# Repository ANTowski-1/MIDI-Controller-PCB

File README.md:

# MIDI-Controller-PCB

Before building using 1st revision think it through, but if you are interested in 2nd revision, it will probably be done in the end of the year, based on interest, so create an issue or write to me directly to let me know that you'd like to see it!

This Repo contains Ki-Cad projects of MIDI-Controller PCB.
Whole documentation can be found in separate repo: ANTowski-1/MIDI-Controller.
(As of end of September 2026, documentations is not made as for code still being developed)

This is an Hobbyist-made project, that isn't connected with MIDI Association in any way, apart from utilizing the MIDI 2.0 standard.

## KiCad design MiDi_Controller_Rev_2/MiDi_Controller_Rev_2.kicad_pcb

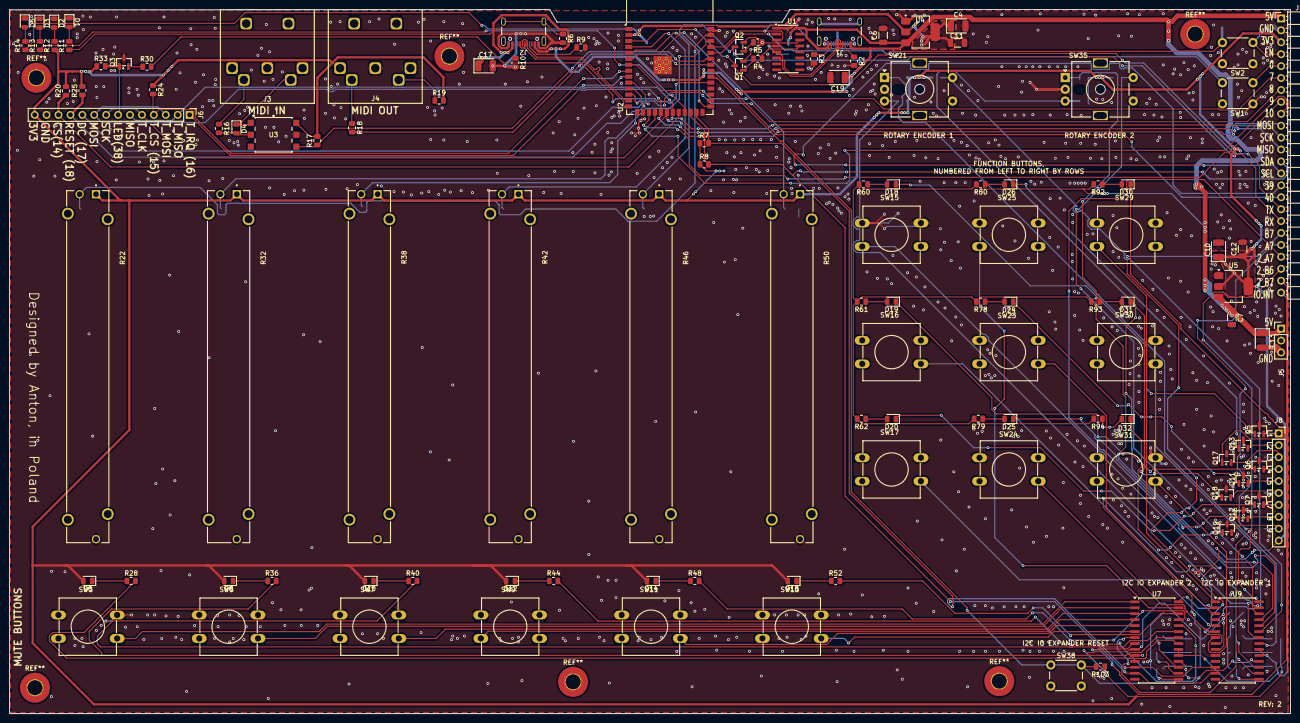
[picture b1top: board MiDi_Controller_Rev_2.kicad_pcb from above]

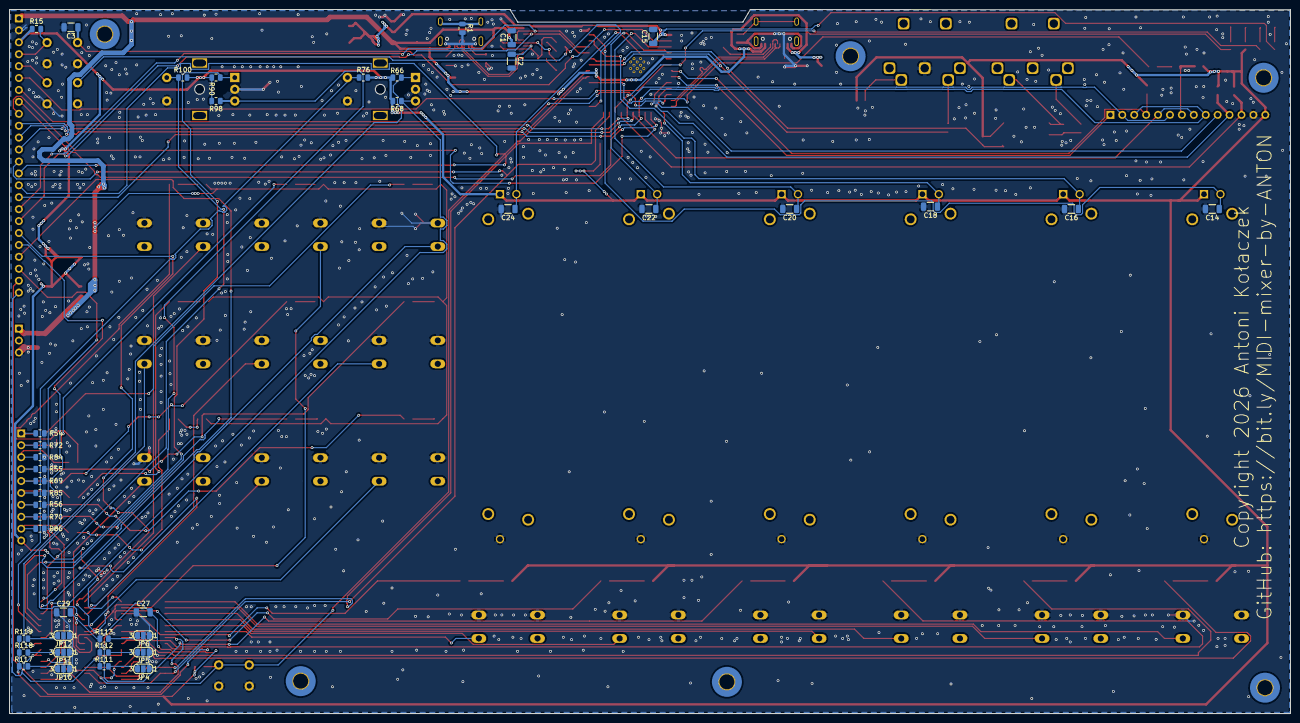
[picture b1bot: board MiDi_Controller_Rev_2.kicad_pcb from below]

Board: 2 copper layers, 272.9 x 150.0 mm, 161 parts (41 on the bottom side), 138 nets.

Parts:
C1, C2, C14, C15, C16, C18, C20, C22, C24: 100nF; C_1206_3216Metric
C3: 1u; C_1206_3216Metric
C4, C10: C_Polarized; CP_EIA-3528-21_Kemet-B
C6, C7, C11, C12, C27, C29: 100n; C_1206_3216Metric
C13, C17, C19: 10µ C_Polarized; CP_EIA-3528-21_Kemet-B
D1, D18, D19, D20, D24, D25, D26, D30, D31, D32: BLUE; LED_0805_2012Metric
D2, D5: GREEN; LED_0805_2012Metric
D3, D6, D8, D10, D12, D14, D16: RED; LED_0805_2012Metric
D4: D; D_0805_2012Metric
J1, J2: USB_C_Receptacle_USB2.0_16P; USB_C_Receptacle_GCT_USB4105-xx-A_16P_TopMnt_Horizontal
J3, J4: DIN-5; DIN-5-lumberg-0105
J5: Conn_01x03_Pin; PinHeader_1x03_P2.54mm_Vertical
J6: Display; PinHeader_1x14_P2.54mm_Vertical
J8: KEYPAD_LEDS; PinSocket_1x10_P2.54mm_Vertical
J10: Conn_01x24_Pin; PinHeader_1x24_P2.54mm_Horizontal
JP4, JP5, JP6, JP10, JP11, JP12: Jumper_3_Bridged12; SolderJumper-3_P1.3mm_Open_RoundedPad1.0x1.5mm_NumberLabels
Q1, Q2: BC817; SOT-23
Q3, Q5, Q6, Q7, Q11, Q12, Q13, Q17, Q18, Q19: NMOS; SOT-23
R1, R6: 1M; R_0805_2012Metric
R2, R3, R9, R10: 5k1; R_0805_2012Metric
R4, R5, R20, R24, R25, R30, R33, R54, R55, R56, R69, R70, R72, R84, R85, R86: 10K; R_0805_2012Metric
R7, R8: 4k7; R_0805_2012Metric
R11, R60, R61, R62, R78, R79, R80, R92, R93, R94: 110R; R_0805_2012Metric
R12, R14: 47R; R_0805_2012Metric
R13, R28, R36, R40, R44, R48, R52: 82R; R_0805_2012Metric
R15: 5.1K; R_0805_2012Metric
R16, R18: 220R; R_0805_2012Metric
R17: 680R; R_0805_2012Metric
R19: 33R; R_0805_2012Metric
R22, R32, R38, R42, R46, R50: PTA6043-2015DPB103; TRIM_PTA6043-2015DPB103
R66, R68, R76, R90, R98, R100, R103, R111, R112, R113, R117, R118, R119: 10k; R_0805_2012Metric
SW1, SW2: TS-1088-AR02016; SW_PUSH_6mm_H5mm
SW3, SW5, SW7, SW9, SW11, SW13, SW15, SW16, SW17, SW23, SW24, SW25, SW29, SW30, SW31: SW_Push; SW_PUSH-12mm
SW21, SW35: RotaryEncoder_Switch; RotaryEncoder_Alps_EC11E-Switch_Vertical_H20mm_MountingHoles
SW38: SW_Push; SW_PUSH_6mm_H4.3mm
U1: CH340C; SOIC-16_3.9x9.9mm_P1.27mm
U2: ESP32-S3-WROOM-1
U3: H11L1; H11L1STA_EVE
U4, U5: AMS1117-3.3; SOT-223-3_TabPin2
U7, U9: MCP23017x-x-SO; SOIC-28W_7.5x17.9mm_P1.27mm

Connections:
2_GPA0: R28.2, U7.21 (GPA0)
2_GPA1: R36.2, U7.22 (GPA1)
2_GPA2: R40.2, U7.23 (GPA2)
2_GPA3: R44.2, U7.24 (GPA3)
2_GPA4: R48.2, U7.25 (GPA4)
2_GPA5: R52.2, U7.26 (GPA5)
2_GPA6: SW25.2, U7.27 (GPA6)
2_GPA7: J10.21, U7.28 (GPA7)
2_GPB0: SW3.2, U7.1 (GPB0)
2_GPB1: SW5.2, U7.2 (GPB1)
2_GPB2: SW7.2, U7.3 (GPB2)
2_GPB3: SW9.2, U7.4 (GPB3)
2_GPB4: SW11.2, U7.5 (GPB4)
2_GPB5: SW13.2, U7.6 (GPB5)
2_GPB6: J10.22, U7.7 (GPB6)
2_GPB7: J10.23, U7.8 (GPB7)
+3V3: C10.1, C12.1, C27.2, C29.2, D6.2 (A), D8.2 (A), D10.2 (A), D12.2 (A), D14.2 (A), D16.2 (A), J6.14, J8.10, J10.3, R7.1, R8.1, R12.1, R15.1, R17.2, R19.2, R20.2, R22.1, R24.1, R25.2, R32.1, R33.1, R38.1, R42.1, R46.1, R50.1, R66.2, R68.2, R76.2, R90.2, R98.2, R100.2, R103.1, R111.1, R112.1, R113.1, R117.1, R118.1, R119.1, U3.6, U5.2 (VO), U7.9 (V_{DD}), U9.9 (V_{DD})
+5V: C1.1, C6.1, C7.1, C13.1, C17.1, C19.1, J1.A4 (VBUS), J1.A9 (VBUS), J1.B4 (VBUS), J1.B9 (VBUS), J2.A4 (VBUS), J2.A9 (VBUS), J2.B4 (VBUS), J2.B9 (VBUS), J5.1, J10.1, R11.1, R60.2, R61.2, R62.2, R78.2, R79.2, R80.2, R92.2, R93.2, R94.2, U1.16 (VCC), U4.3 (VI), U5.3 (VI)
A0: JP10.2 (C), U9.15 (A0)
A0_2: JP4.2 (C), U7.15 (A0)
A1: JP11.2 (C), U9.16 (A1)
A1_2: JP5.2 (C), U7.16 (A1)
A2: JP12.2 (C), U9.17 (A2)
A2_2: JP6.2 (C), U7.17 (A2)
D+: J2.A6 (D+), J2.B6 (D+), U2.14 (USB_D+)
D-: J2.A7 (D-), J2.B7 (D-), U2.13 (USB_D-)
DS+: J1.A6 (D+), J1.B6 (D+), U1.5 (UD+)
DS-: J1.A7 (D-), J1.B7 (D-), U1.6 (UD-)
EN: C3.1, J10.4, Q1.3 (C), R15.2, SW2.2, U2.3 (EN)
GND: C1.2, C2.2, C3.2, C4.2, C6.2, C7.2, C10.2, C11.2, C12.2, C13.2, C14.2, C15.2, C16.2, C17.2, C18.2, C19.2, C20.2, C22.2, C24.2, C27.1, C29.1, D1.1 (K), D2.1 (K), D3.1 (K), D5.1 (K), J1.A1 (GND), J1.A12 (GND), J1.B1 (GND), J1.B12 (GND), J2.A1 (GND), J2.A12 (GND), J2.B1 (GND), J2.B12 (GND), J4.2, J5.3, J6.13, J10.2, JP4.1 (A), JP5.1 (A), JP6.1 (A), JP10.1 (A), JP11.1 (A), JP12.1 (A), Q3.3 (S), Q5.3 (S), Q6.3 (S), Q7.3 (S), Q11.3 (S), Q12.3 (S), Q13.3 (S), Q17.3 (S), Q18.3 (S), Q19.3 (S), R1.2, R2.2, R3.2, R6.2, R9.2, R10.2, R22.3, R32.3, R38.3, R42.3, R46.3, R50.3, R54.1, R55.1, R56.1, R69.1, R70.1, R72.1, R84.1, R85.1, R86.1, SW1.1, SW2.1, SW3.1, SW5.1, SW7.1, SW9.1, SW11.1, SW13.1, SW15.1, SW16.1, SW17.1, SW21.C, SW21.S1, SW23.1, SW24.1, SW25.1, SW29.1, SW30.1, SW31.1, SW35.C, SW35.S1, SW38.2, U1.1 (GND), U2.1 (GND), U2.40 (GND), U2.41 (GND), U3.5, U4.1 (GND), U5.1 (GND), U7.10 (V_{SS}), U9.10 (V_{SS})
GPA0: R66.1, SW21.A, U9.21 (GPA0)
GPA1: R68.1, SW21.B, U9.22 (GPA1)
GPA2: R76.1, SW21.S2, U9.23 (GPA2)
GPA3: R90.1, SW35.A, U9.24 (GPA3)
GPA4: R98.1, SW35.B, U9.25 (GPA4)
GPA5: R100.1, SW35.S2, U9.26 (GPA5)
GPA6: SW15.2, U9.27 (GPA6)
GPA7: J10.20, U9.28 (GPA7)
GPB0: SW29.2, U9.1 (GPB0)
GPB1: SW16.2, U9.2 (GPB1)
GPB2: SW23.2, U9.3 (GPB2)
GPB3: SW30.2, U9.4 (GPB3)
GPB4: SW17.2, U9.5 (GPB4)
GPB5: SW24.2, U9.6 (GPB5)
GPB6: SW31.2, U9.7 (GPB6)
GPB7: J10.19, U9.8 (GPB7)
GPIO0: J10.5, Q2.3 (C), SW1.2, U2.27 (IO0)
GPIO1: C14.1, R22.2, U2.39 (IO1)
GPIO2: C16.1, R32.2, U2.38 (IO2)
GPIO3: C18.1, R38.2, U2.15 (IO3)
GPIO4: C20.1, R42.2, U2.4 (IO4)
GPIO5: C22.1, R46.2, U2.5 (IO5)
GPIO6: C24.1, R50.2, U2.6 (IO6)
GPIO7: J10.6, U2.7 (IO7)
GPIO8: J10.7, U2.12 (IO8)
GPIO9: J10.8, U2.17 (IO9)
GPIO10: J10.9, U2.18 (IO10)
GPIO11: J6.3, J6.9, J10.10, U2.19 (IO11)
GPIO12: J6.5, J6.8, J10.11, U2.20 (IO12)
GPIO13: J6.2, J6.6, J10.12, U2.21 (IO13)
GPIO14: J6.12, R20.1, U2.22 (IO14)
GPIO15: J6.4, R24.2, U2.8 (IO15)
GPIO16: J6.1, U2.9 (IO16)
GPIO17: J6.10, U2.10 (IO17)
GPIO18: J6.11, R25.1, U2.11 (IO18)
GPIO21: R13.1, U2.23 (IO21)
GPIO38: R30.2, U2.31 (IO38)
GPIO39: J10.15, R103.2, SW38.1, U2.32 (IO39), U7.18 (~RESET), U9.18 (~RESET)
GPIO40: J10.16, U2.33 (IO40)
GPIO41: R18.2, U2.34 (IO41)
GPIO42: R17.1, U2.35 (IO42), U3.4
INTA: J10.24, U7.19 (INTB), U7.20 (INTA), U9.19 (INTB), U9.20 (INTA)
unnamed: D1.2 (A), R11.2
unnamed: D2.2 (A), R12.2
unnamed: D3.2 (A), R13.2
unnamed: D4.2 (A), R16.2, U3.2
unnamed: D4.1 (K), J3.5, U3.1
unnamed: D5.2 (A), R14.2
unnamed: D6.1 (K), R28.1
unnamed: D8.1 (K), R36.1
unnamed: D10.1 (K), R40.1
unnamed: D12.1 (K), R44.1
unnamed: D14.1 (K), R48.1
unnamed: D16.1 (K), R52.1
unnamed: D18.2 (A), R60.1
unnamed: D18.1 (K), Q5.1 (D)
unnamed: D19.2 (A), R61.1
unnamed: D19.1 (K), Q6.1 (D)
unnamed: D20.2 (A), R62.1
unnamed: D20.1 (K), Q7.1 (D)
unnamed: D24.2 (A), R78.1
unnamed: D24.1 (K), Q11.1 (D)
unnamed: D25.2 (A), R79.1
unnamed: D25.1 (K), Q12.1 (D)
unnamed: D26.2 (A), R80.1
unnamed: D26.1 (K), Q13.1 (D)
unnamed: D30.2 (A), R92.1
unnamed: D30.1 (K), Q17.1 (D)
unnamed: D31.2 (A), R93.1
unnamed: D31.1 (K), Q18.1 (D)
unnamed: D32.2 (A), R94.1
unnamed: D32.1 (K), Q19.1 (D)
unnamed: J1.A5 (CC1), R2.1
unnamed: J1.B5 (CC2), R3.1
unnamed: J1.SH (SHIELD), R1.1
unnamed: J2.A5 (CC1), R9.1
unnamed: J2.B5 (CC2), R10.1
unnamed: J2.SH (SHIELD), R6.1
unnamed: J3.4, R16.1
unnamed: J4.4, R18.1
unnamed: J4.5, R19.1
unnamed: J6.7, Q3.1 (D), R33.2
unnamed: JP4.3 (B), R111.2
unnamed: JP5.3 (B), R112.2
unnamed: JP6.3 (B), R113.2
unnamed: JP10.3 (B), R117.2
unnamed: JP11.3 (B), R118.2
unnamed: JP12.3 (B), R119.2
unnamed: Q1.1 (B), R4.2
unnamed: Q1.2 (E), R5.1, U1.14 (~RTS)
unnamed: Q2.1 (B), R5.2
unnamed: Q2.2 (E), R4.1, U1.13 (~DTR)
unnamed: Q3.2 (G), R30.1
unnamed: C2.1, U1.4 (V3)
RX0: J10.18, U1.2 (TXD), U2.36 (RXD0)
SCL: J10.14, R7.2, U2.25 (IO48), U7.12 (SCK), U9.12 (SCK)
SDA: J10.13, R8.2, U2.24 (IO47), U7.13 (SDA), U9.13 (SDA)
SL1: J8.1, Q5.2 (G), R54.2
SL2: J8.2, Q13.2 (G), R72.2
SL3: J8.3, Q17.2 (G), R84.2
SL4: J8.4, Q6.2 (G), R55.2
SL5: J8.5, Q11.2 (G), R69.2
SL6: J8.6, Q18.2 (G), R85.2
SL7: J8.7, Q7.2 (G), R56.2
SL8: J8.8, Q12.2 (G), R70.2
SL9: J8.9, Q19.2 (G), R86.2
TX0: J10.17, U1.3 (RXD), U2.37 (TXD0)
VCC: C4.1, C11.1, C15.1, R14.1, U2.2 (3V3), U4.2 (VO)

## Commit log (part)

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2026-05-17 Adding README.md
2026-05-17 Adding PCB files
2026-05-17 Modify README.md
2026-05-17 Readme.md modification
2026-05-17 Remove technic shell file
2026-05-17 Revert "Adding PCB files"
    This reverts commit 5f1f5a5b989860db797b21627ae796cebe1ef32a.
2026-05-18 Restore Both PCB revisions

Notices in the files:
MiDi_Controller_Rev_2/MiDi_Controller_Rev_2.kicad_pcb:
Copyright 2026 Antoni Kołaczek
Copyright Antoni Kołaczek 2026.
This source describes Open Hardware and is licensed under CERN-OHL-S V2+
under the terms of the CERN-OHL-S v2
QUALITY AND FITNESS FOR A PARTICULAR PURPOSE. Please see
the CERN-OHL-S v2 for applicable conditions.
As per CERN-OHL-S v2 section 4, should You produce hardware based
